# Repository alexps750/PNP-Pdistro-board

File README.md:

# PNP-Pdistro-board
Pick and Place Machine Main Power Distibution Board. 120VAC/12VDC input and 120VAC/12V+5V output

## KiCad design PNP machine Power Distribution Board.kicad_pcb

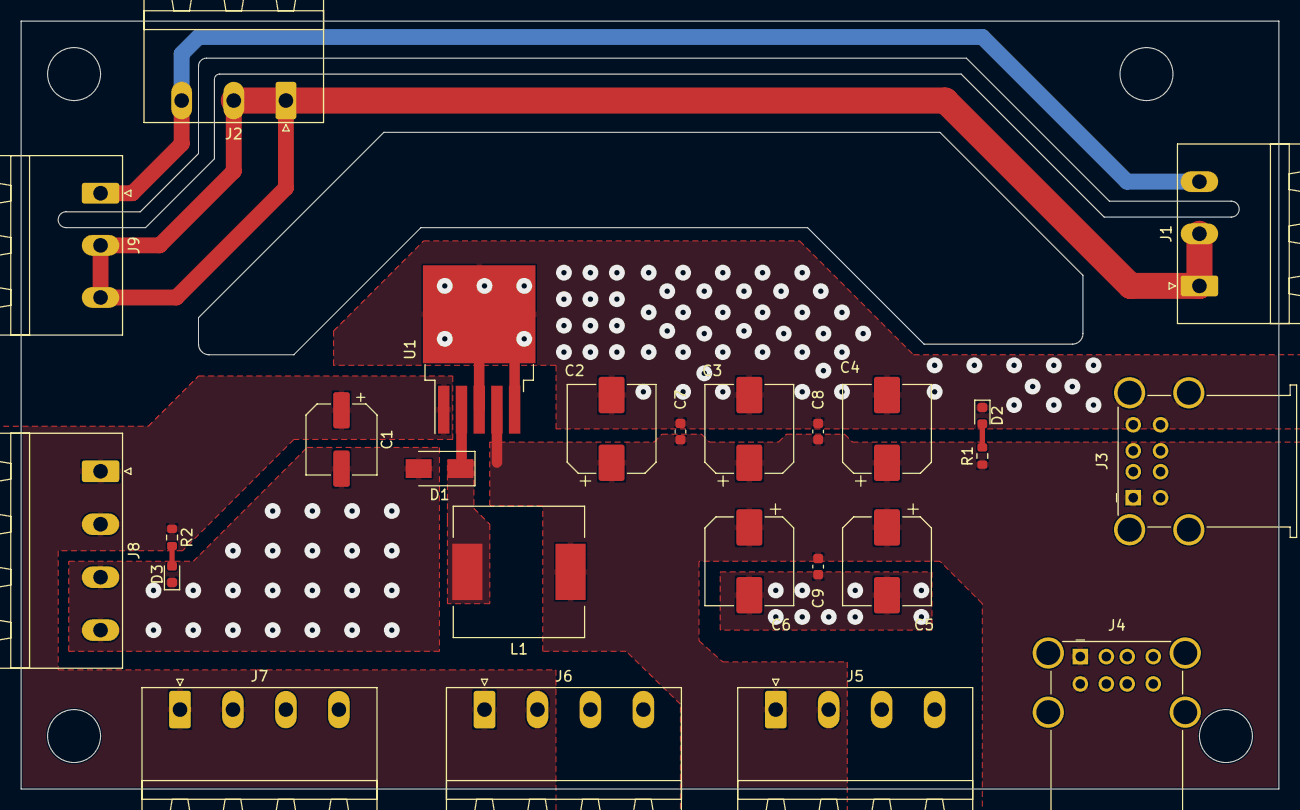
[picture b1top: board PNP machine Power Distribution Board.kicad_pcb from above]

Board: 2 copper layers, 120.6 x 73.7 mm, 25 parts (0 on the bottom side), 8 nets.

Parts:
C1: 100U; CP_Elec_6.3x5.3
C2, C3, C4, C5, C6: 220u; CP_Elec_8x10
C7, C8, C9: C; C_0603_1608Metric
D1: 1N5822; D_SMA
D2: BLU; LED_0603_1608Metric
D3: GRN; LED_0603_1608Metric
J1, J2: 120VAC INPUT; PhoenixContact_MSTBA_2,5_3-G_1x03_P5.00mm_Horizontal
J3, J4: USB_A; USB_A_Wuerth_61400826021_Horizontal_Stacked
J5: 5VAUX_OUT; PhoenixContact_MSTBA_2,5_4-G-5,08_1x04_P5.08mm_Horizontal
J6: 12VOUTPUT; PhoenixContact_MSTBA_2,5_4-G-5,08_1x04_P5.08mm_Horizontal
J7: 12VAUX_OUTPUT; PhoenixContact_MSTBA_2,5_4-G-5,08_1x04_P5.08mm_Horizontal
J8: 12V DC PWR INTPUT; PhoenixContact_MSTBA_2,5_4-G-5,08_1x04_P5.08mm_Horizontal
J9: 120VAC_OUT; PhoenixContact_MSTBA_2,5_3-G_1x03_P5.00mm_Horizontal
L1: 100U; L_12x12mm_H8mm
R1: 1K; R_0603_1608Metric
R2: 4K7; R_0603_1608Metric
U1: LM2576S-5; TO-263-5_TabPin3

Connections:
/5V: C2.1, C3.1, C4.1, C5.1, C6.1, C7.1, C8.1, C9.1, J3.1, J3.5, J4.1, J4.5, J5.1, J5.2, L1.1, R1.1, U1.4
/12V: C1.1, J6.1, J6.2, J7.1, J7.2, J8.1, J8.2, R2.1, U1.1
/GND: J1.1, J1.2, J2.1, J2.2, J9.2, J9.3
/GNDPWR: C1.2, C2.2, C3.2, C4.2, C5.2, C6.2, C7.2, C8.2, C9.2, D1.2, D2.1, D3.1, J3.4, J3.8, J3.9, J4.4, J4.8, J4.9, J5.3, J5.4, J6.3, J6.4, J7.3, J7.4, J8.3, J8.4, U1.3, U1.5
/LINE: J1.3, J2.3, J9.1
unnamed: D1.1, L1.2, U1.2
unnamed: D2.2, R1.2
unnamed: D3.2, R2.2

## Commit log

2021-04-01 revision 1 of project with gerbers
